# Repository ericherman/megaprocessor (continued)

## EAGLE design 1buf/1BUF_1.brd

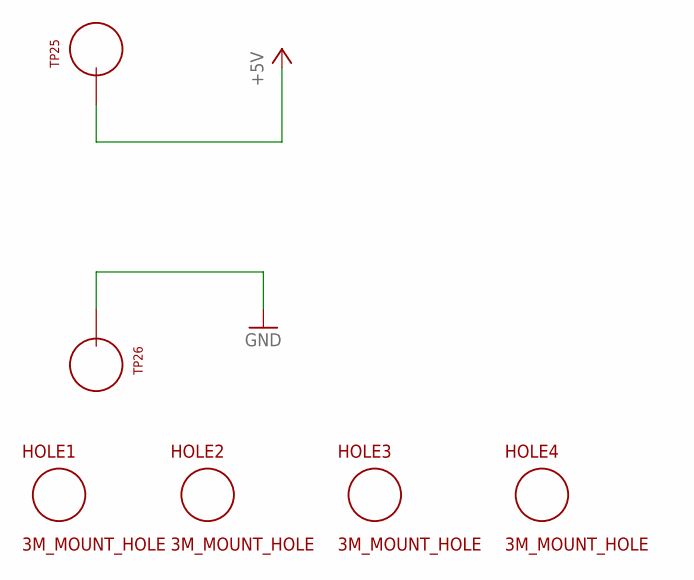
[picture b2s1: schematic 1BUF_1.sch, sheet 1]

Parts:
HOLE1, HOLE2, HOLE3, HOLE4: 3M_MOUNT_HOLE; 3M_HOLE
TP25, TP26: TEST_LOOP

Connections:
+5V: TP25.P$1; also elsewhere on the board
GND: TP26.P$1; also elsewhere on the board

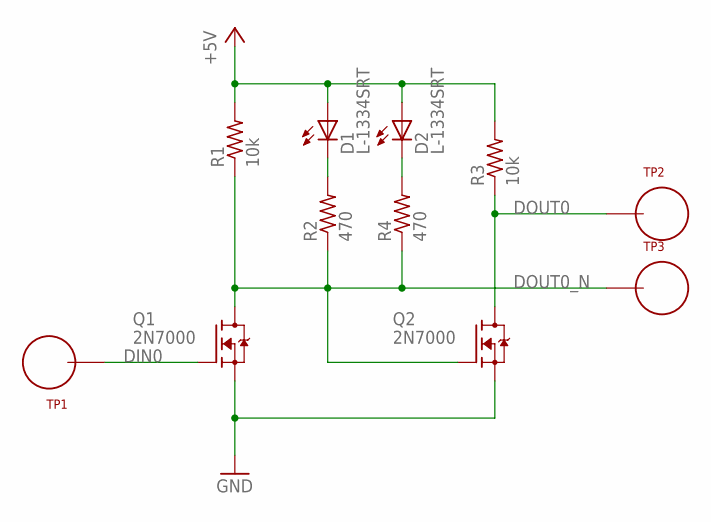
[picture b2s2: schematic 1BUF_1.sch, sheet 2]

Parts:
D1, D2: L-1334SRT; LED3MM
Q1, Q2: 2N7000; TO92-DGS
R1, R3: 10k; R_P2INCH
R2, R4: 470; R_P2INCH
TP1, TP2, TP3: TEST_LOOP

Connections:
+5V: D1.A, D2.A, R1.2, R3.2; also elsewhere on the board
DIN0: Q1.G, TP1.P$1
DOUT0: Q2.D, R3.1, TP2.P$1
DOUT0_N: Q1.D, Q2.G, R1.1, R2.1, R4.1, TP3.P$1
GND: Q1.S, Q2.S; also elsewhere on the board
unnamed: D2.K (C), R4.2
unnamed: D1.K (C), R2.2

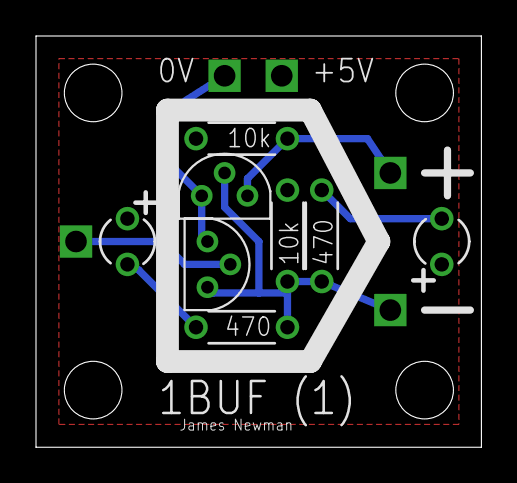
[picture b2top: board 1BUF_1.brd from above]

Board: 2 copper layers, 24.7 x 22.8 mm, 17 parts (0 on the bottom side), 7 nets.

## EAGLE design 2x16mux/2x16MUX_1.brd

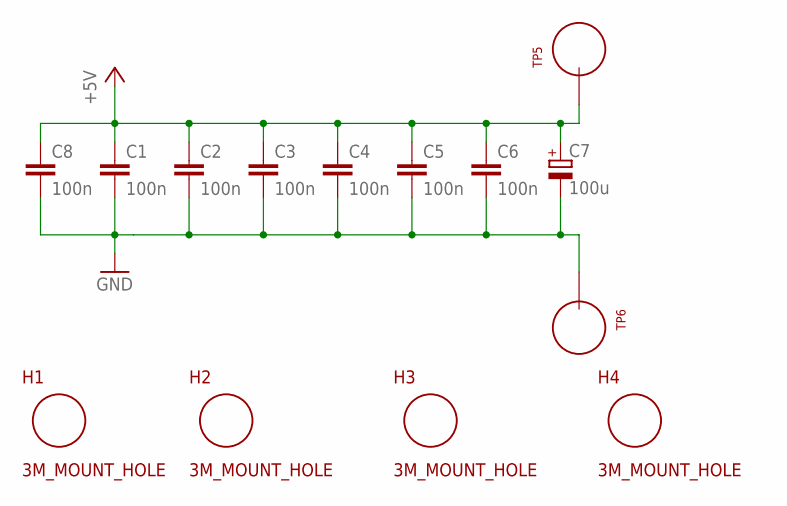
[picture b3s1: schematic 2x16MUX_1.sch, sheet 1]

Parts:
C1, C2, C3, C4, C5, C6, C8: 100n; CAP_P2INCH
C7: 100u; POLARISED_CAP_2P5_6P3MM
H1, H2, H3, H4: 3M_MOUNT_HOLE; 3M_HOLE
TP5, TP6: TEST_LOOP

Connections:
+5V: C1.1, C2.1, C3.1, C4.1, C5.1, C6.1, C7.A, C8.1, TP5.P$1; also elsewhere on the board
GND: C1.2, C2.2, C3.2, C4.2, C5.2, C6.2, C7.K, C8.2, TP6.P$1; also elsewhere on the board

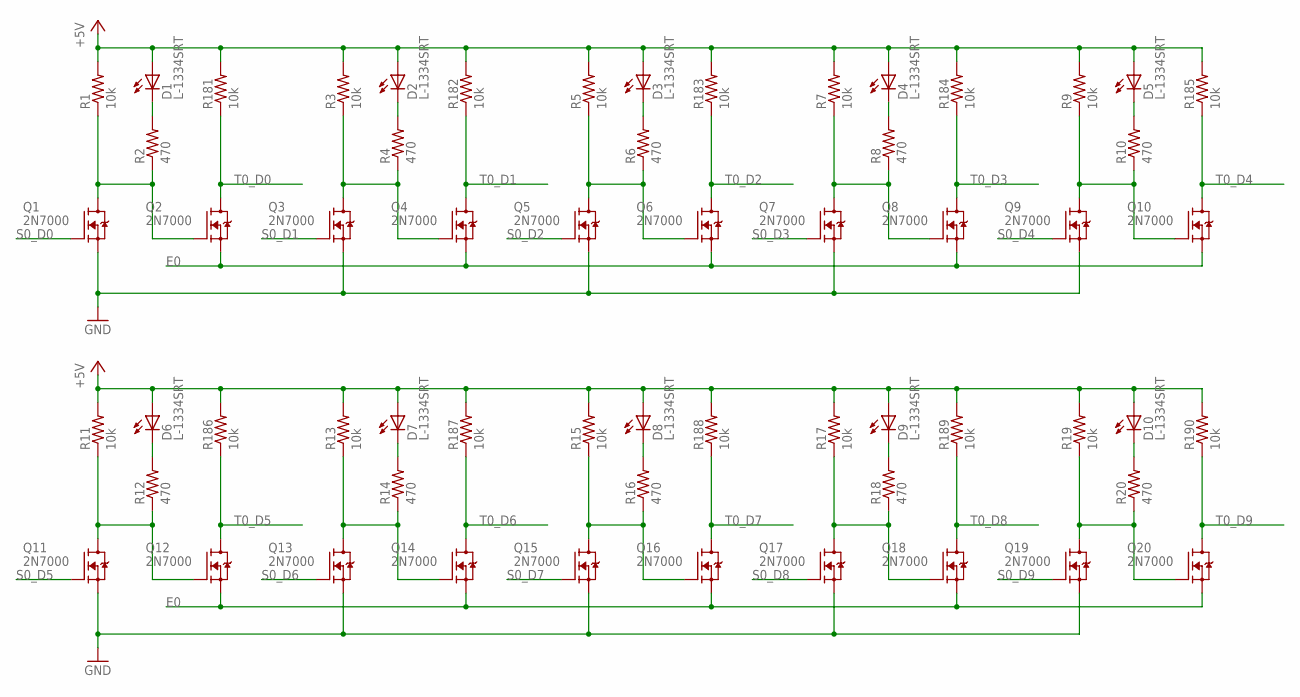
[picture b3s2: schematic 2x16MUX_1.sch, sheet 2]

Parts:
D1, D2, D3, D4, D5, D6, D7, D8, D9, D10: L-1334SRT; LED3MM
Q1, Q2, Q3, Q4, Q5, Q6, Q7, Q8, Q9, Q10, Q11, Q12, Q13, Q14, Q15, Q16, Q17, Q18, Q19, Q20: 2N7000; TO92-DGS
R1, R3, R5, R7, R9, R11, R13, R15, R17, R19, R181, R182, R183, R184, R185, R186, R187, R188, R189, R190: 10k; R_P2INCH
R2, R4, R6, R8, R10, R12, R14, R16, R18, R20: 470; R_P2INCH

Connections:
+5V: D1.A, D2.A, D3.A, D4.A, D5.A, D6.A, D7.A, D8.A, D9.A, D10.A, R1.2, R3.2, R5.2, R7.2, R9.2, R11.2, R13.2, R15.2, R17.2, R19.2, R181.2, R182.2, R183.2, R184.2, R185.2, R186.2, R187.2, R188.2, R189.2, R190.2; also elsewhere on the board
E0: Q2.S, Q4.S, Q6.S, Q8.S, Q10.S, Q12.S, Q14.S, Q16.S, Q18.S, Q20.S; also elsewhere on the board
GND: Q1.S, Q3.S, Q5.S, Q7.S, Q9.S, Q11.S, Q13.S, Q15.S, Q17.S, Q19.S; also elsewhere on the board
unnamed: Q3.D, Q4.G, R3.1, R4.1
unnamed: Q1.D, Q2.G, R1.1, R2.1
unnamed: D1.K (C), R2.2
unnamed: D2.K (C), R4.2
unnamed: Q5.D, Q6.G, R5.1, R6.1
unnamed: D3.K (C), R6.2
unnamed: Q7.D, Q8.G, R7.1, R8.1
unnamed: D4.K (C), R8.2
unnamed: Q9.D, Q10.G, R9.1, R10.1
unnamed: D5.K (C), R10.2
unnamed: Q11.D, Q12.G, R11.1, R12.1
unnamed: D6.K (C), R12.2
unnamed: Q13.D, Q14.G, R13.1, R14.1
unnamed: D7.K (C), R14.2
unnamed: Q15.D, Q16.G, R15.1, R16.1
unnamed: D8.K (C), R16.2
unnamed: Q17.D, Q18.G, R17.1, R18.1
unnamed: D9.K (C), R18.2
unnamed: Q19.D, Q20.G, R19.1, R20.1
unnamed: D10.K (C), R20.2
S0_D0: Q1.G; also elsewhere on the board
S0_D1: Q3.G; also elsewhere on the board
S0_D2: Q5.G; also elsewhere on the board
S0_D3: Q7.G; also elsewhere on the board
S0_D4: Q9.G; also elsewhere on the board
S0_D5: Q11.G; also elsewhere on the board
S0_D6: Q13.G; also elsewhere on the board
S0_D7: Q15.G; also elsewhere on the board
S0_D8: Q17.G; also elsewhere on the board
S0_D9: Q19.G; also elsewhere on the board
T0_D0: Q2.D, R181.1; also elsewhere on the board
T0_D1: Q4.D, R182.1; also elsewhere on the board
T0_D2: Q6.D, R183.1; also elsewhere on the board
T0_D3: Q8.D, R184.1; also elsewhere on the board
T0_D4: Q10.D, R185.1; also elsewhere on the board
T0_D5: Q12.D, R186.1; also elsewhere on the board
T0_D6: Q14.D, R187.1; also elsewhere on the board
T0_D7: Q16.D, R188.1; also elsewhere on the board
T0_D8: Q18.D, R189.1; also elsewhere on the board
T0_D9: Q20.D, R190.1; also elsewhere on the board

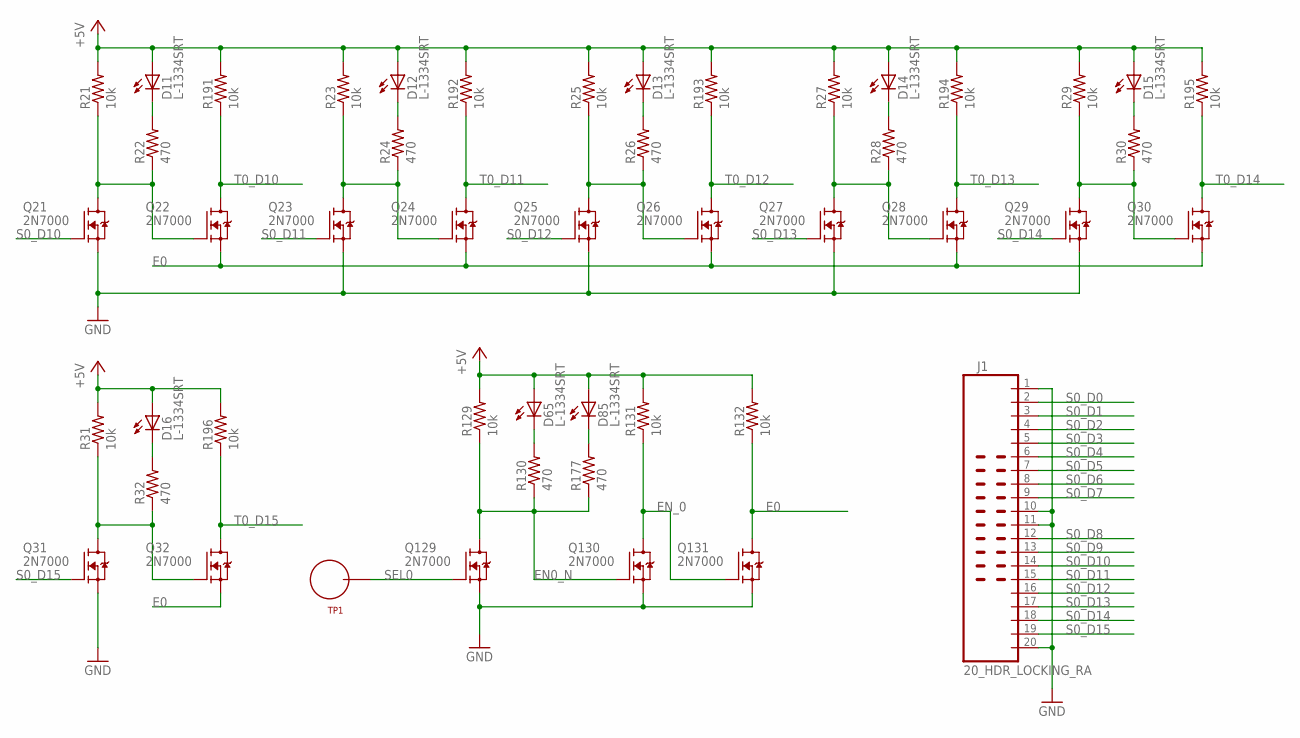
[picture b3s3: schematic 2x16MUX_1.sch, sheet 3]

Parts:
D11, D12, D13, D14, D15, D16, D65, D85: L-1334SRT; LED3MM
J1: 20_HDR_LOCKING_RA
Q21, Q22, Q23, Q24, Q25, Q26, Q27, Q28, Q29, Q30, Q31, Q32, Q129, Q130, Q131: 2N7000; TO92-DGS
R21, R23, R25, R27, R29, R31, R129, R131, R132, R191, R192, R193, R194, R195, R196: 10k; R_P2INCH
R22, R24, R26, R28, R30, R32, R130, R177: 470; R_P2INCH
TP1: TEST_LOOP

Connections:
+5V: D11.A, D12.A, D13.A, D14.A, D15.A, D16.A, D65.A, D85.A, R21.2, R23.2, R25.2, R27.2, R29.2, R31.2, R129.2, R131.2, R132.2, R191.2, R192.2, R193.2, R194.2, R195.2, R196.2; also elsewhere on the board
E0: Q22.S, Q24.S, Q26.S, Q28.S, Q30.S, Q32.S, Q131.D, R132.1; also elsewhere on the board
EN0_N: Q129.D, Q130.G, R129.1, R130.1, R177.1
EN_0: Q130.D, Q131.G, R131.1
GND: J1.1, J1.10, J1.11, J1.20, Q21.S, Q23.S, Q25.S, Q27.S, Q29.S, Q31.S, Q129.S, Q130.S, Q131.S; also elsewhere on the board
unnamed: Q21.D, Q22.G, R21.1, R22.1
unnamed: D11.K (C), R22.2
unnamed: Q23.D, Q24.G, R23.1, R24.1
unnamed: D12.K (C), R24.2
unnamed: Q25.D, Q26.G, R25.1, R26.1
unnamed: D13.K (C), R26.2
unnamed: Q27.D, Q28.G, R27.1, R28.1
unnamed: D14.K (C), R28.2
unnamed: Q29.D, Q30.G, R29.1, R30.1
unnamed: D15.K (C), R30.2
unnamed: Q31.D, Q32.G, R31.1, R32.1
unnamed: D16.K (C), R32.2
unnamed: D65.K (C), R130.2
unnamed: D85.K (C), R177.2
S0_D0: J1.2; also elsewhere on the board
S0_D1: J1.3; also elsewhere on the board
S0_D2: J1.4; also elsewhere on the board
S0_D3: J1.5; also elsewhere on the board
S0_D4: J1.6; also elsewhere on the board
S0_D5: J1.7; also elsewhere on the board
S0_D6: J1.8; also elsewhere on the board
S0_D7: J1.9; also elsewhere on the board
S0_D8: J1.12; also elsewhere on the board
S0_D9: J1.13; also elsewhere on the board
S0_D10: J1.14, Q21.G
S0_D11: J1.15, Q23.G
S0_D12: J1.16, Q25.G
S0_D13: J1.17, Q27.G
S0_D14: J1.18, Q29.G
S0_D15: J1.19, Q31.G
SEL0: Q129.G, TP1.P$1
T0_D10: Q22.D, R191.1; also elsewhere on the board
T0_D11: Q24.D, R192.1; also elsewhere on the board
T0_D12: Q26.D, R193.1; also elsewhere on the board
T0_D13: Q28.D, R194.1; also elsewhere on the board
T0_D14: Q30.D, R195.1; also elsewhere on the board
T0_D15: Q32.D, R196.1; also elsewhere on the board

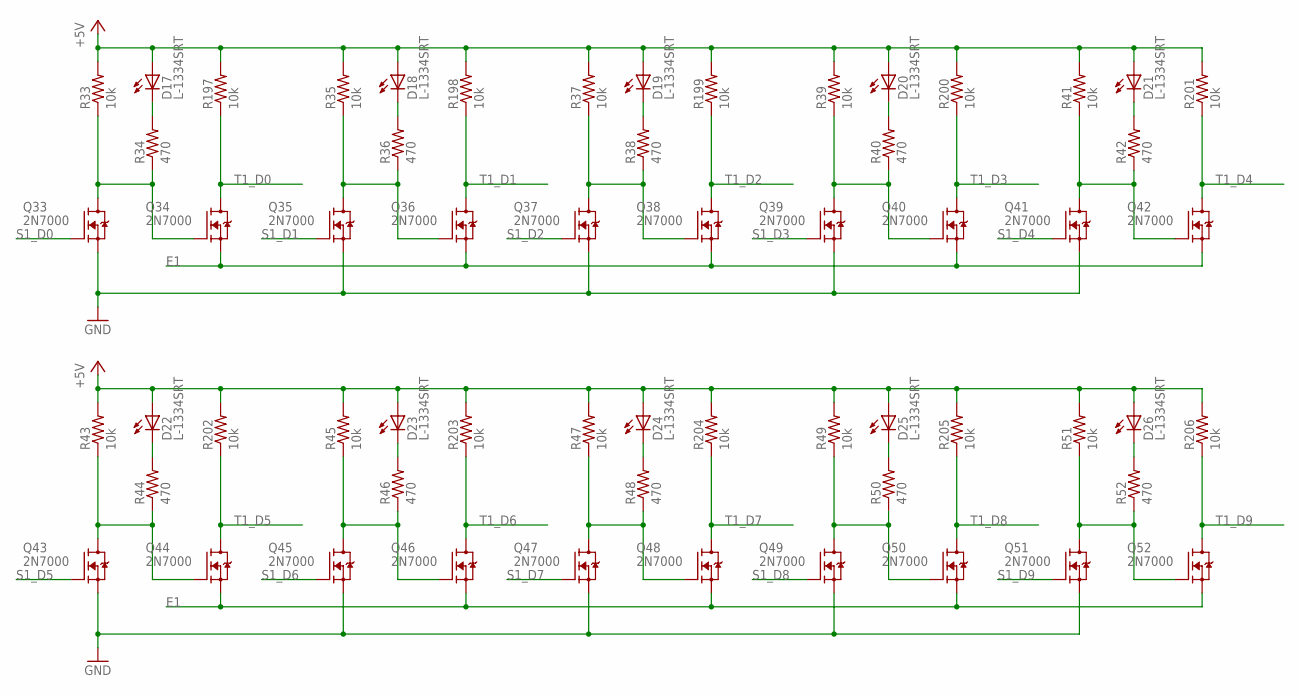
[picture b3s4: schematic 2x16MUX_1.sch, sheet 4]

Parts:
D17, D18, D19, D20, D21, D22, D23, D24, D25, D26: L-1334SRT; LED3MM
Q33, Q34, Q35, Q36, Q37, Q38, Q39, Q40, Q41, Q42, Q43, Q44, Q45, Q46, Q47, Q48, Q49, Q50, Q51, Q52: 2N7000; TO92-DGS
R33, R35, R37, R39, R41, R43, R45, R47, R49, R51, R197, R198, R199, R200, R201, R202, R203, R204, R205, R206: 10k; R_P2INCH
R34, R36, R38, R40, R42, R44, R46, R48, R50, R52: 470; R_P2INCH

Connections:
+5V: D17.A, D18.A, D19.A, D20.A, D21.A, D22.A, D23.A, D24.A, D25.A, D26.A, R33.2, R35.2, R37.2, R39.2, R41.2, R43.2, R45.2, R47.2, R49.2, R51.2, R197.2, R198.2, R199.2, R200.2, R201.2, R202.2, R203.2, R204.2, R205.2, R206.2; also elsewhere on the board
E1: Q34.S, Q36.S, Q38.S, Q40.S, Q42.S, Q44.S, Q46.S, Q48.S, Q50.S, Q52.S; also elsewhere on the board
GND: Q33.S, Q35.S, Q37.S, Q39.S, Q41.S, Q43.S, Q45.S, Q47.S, Q49.S, Q51.S; also elsewhere on the board
unnamed: Q33.D, Q34.G, R33.1, R34.1
unnamed: D17.K (C), R34.2
unnamed: Q35.D, Q36.G, R35.1, R36.1
unnamed: D18.K (C), R36.2
unnamed: Q37.D, Q38.G, R37.1, R38.1
unnamed: D19.K (C), R38.2
unnamed: Q39.D, Q40.G, R39.1, R40.1
unnamed: D20.K (C), R40.2
unnamed: Q41.D, Q42.G, R41.1, R42.1
unnamed: D21.K (C), R42.2
unnamed: Q43.D, Q44.G, R43.1, R44.1
unnamed: D22.K (C), R44.2
unnamed: Q45.D, Q46.G, R45.1, R46.1
unnamed: D23.K (C), R46.2
unnamed: Q47.D, Q48.G, R47.1, R48.1
unnamed: D24.K (C), R48.2
unnamed: Q49.D, Q50.G, R49.1, R50.1
unnamed: D25.K (C), R50.2
unnamed: Q51.D, Q52.G, R51.1, R52.1
unnamed: D26.K (C), R52.2
S1_D0: Q33.G; also elsewhere on the board
S1_D1: Q35.G; also elsewhere on the board
S1_D2: Q37.G; also elsewhere on the board
S1_D3: Q39.G; also elsewhere on the board
S1_D4: Q41.G; also elsewhere on the board
S1_D5: Q43.G; also elsewhere on the board
S1_D6: Q45.G; also elsewhere on the board
S1_D7: Q47.G; also elsewhere on the board
S1_D8: Q49.G; also elsewhere on the board
S1_D9: Q51.G; also elsewhere on the board
T1_D0: Q34.D, R197.1; also elsewhere on the board
T1_D1: Q36.D, R198.1; also elsewhere on the board
T1_D2: Q38.D, R199.1; also elsewhere on the board
T1_D3: Q40.D, R200.1; also elsewhere on the board
T1_D4: Q42.D, R201.1; also elsewhere on the board
T1_D5: Q44.D, R202.1; also elsewhere on the board
T1_D6: Q46.D, R203.1; also elsewhere on the board
T1_D7: Q48.D, R204.1; also elsewhere on the board
T1_D8: Q50.D, R205.1; also elsewhere on the board
T1_D9: Q52.D, R206.1; also elsewhere on the board

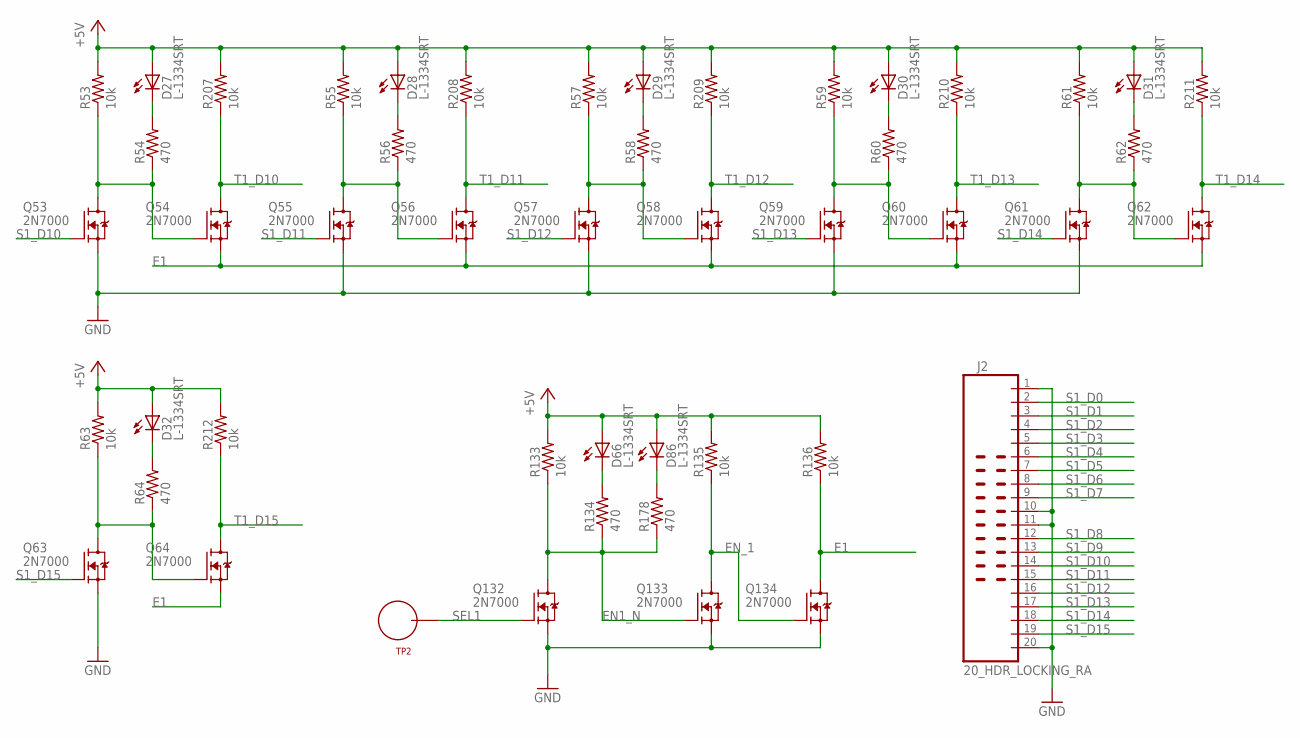
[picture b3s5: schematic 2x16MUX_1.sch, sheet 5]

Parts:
D27, D28, D29, D30, D31, D32, D66, D86: L-1334SRT; LED3MM
J2: 20_HDR_LOCKING_RA
Q53, Q54, Q55, Q56, Q57, Q58, Q59, Q60, Q61, Q62, Q63, Q64, Q132, Q133, Q134: 2N7000; TO92-DGS
R53, R55, R57, R59, R61, R63, R133, R135, R136, R207, R208, R209, R210, R211, R212: 10k; R_P2INCH
R54, R56, R58, R60, R62, R64, R134, R178: 470; R_P2INCH
TP2: TEST_LOOP

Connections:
+5V: D27.A, D28.A, D29.A, D30.A, D31.A, D32.A, D66.A, D86.A, R53.2, R55.2, R57.2, R59.2, R61.2, R63.2, R133.2, R135.2, R136.2, R207.2, R208.2, R209.2, R210.2, R211.2, R212.2; also elsewhere on the board
E1: Q54.S, Q56.S, Q58.S, Q60.S, Q62.S, Q64.S, Q134.D, R136.1; also elsewhere on the board
EN1_N: Q132.D, Q133.G, R133.1, R134.1, R178.1
EN_1: Q133.D, Q134.G, R135.1
GND: J2.1, J2.10, J2.11, J2.20, Q53.S, Q55.S, Q57.S, Q59.S, Q61.S, Q63.S, Q132.S, Q133.S, Q134.S; also elsewhere on the board
unnamed: Q53.D, Q54.G, R53.1, R54.1
unnamed: D27.K (C), R54.2
unnamed: Q55.D, Q56.G, R55.1, R56.1
unnamed: D28.K (C), R56.2
unnamed: Q57.D, Q58.G, R57.1, R58.1
unnamed: D29.K (C), R58.2
unnamed: Q59.D, Q60.G, R59.1, R60.1
unnamed: D30.K (C), R60.2
unnamed: Q61.D, Q62.G, R61.1, R62.1
unnamed: D31.K (C), R62.2
unnamed: Q63.D, Q64.G, R63.1, R64.1
unnamed: D32.K (C), R64.2
unnamed: D66.K (C), R134.2
unnamed: D86.K (C), R178.2
S1_D0: J2.2; also elsewhere on the board
S1_D1: J2.3; also elsewhere on the board
S1_D2: J2.4; also elsewhere on the board
S1_D3: J2.5; also elsewhere on the board
S1_D4: J2.6; also elsewhere on the board
S1_D5: J2.7; also elsewhere on the board
S1_D6: J2.8; also elsewhere on the board
S1_D7: J2.9; also elsewhere on the board
S1_D8: J2.12; also elsewhere on the board
S1_D9: J2.13; also elsewhere on the board
S1_D10: J2.14, Q53.G
S1_D11: J2.15, Q55.G
S1_D12: J2.16, Q57.G
S1_D13: J2.17, Q59.G
S1_D14: J2.18, Q61.G
S1_D15: J2.19, Q63.G
SEL1: Q132.G, TP2.P$1
T1_D10: Q54.D, R207.1; also elsewhere on the board
T1_D11: Q56.D, R208.1; also elsewhere on the board
T1_D12: Q58.D, R209.1; also elsewhere on the board
T1_D13: Q60.D, R210.1; also elsewhere on the board
T1_D14: Q62.D, R211.1; also elsewhere on the board
T1_D15: Q64.D, R212.1; also elsewhere on the board

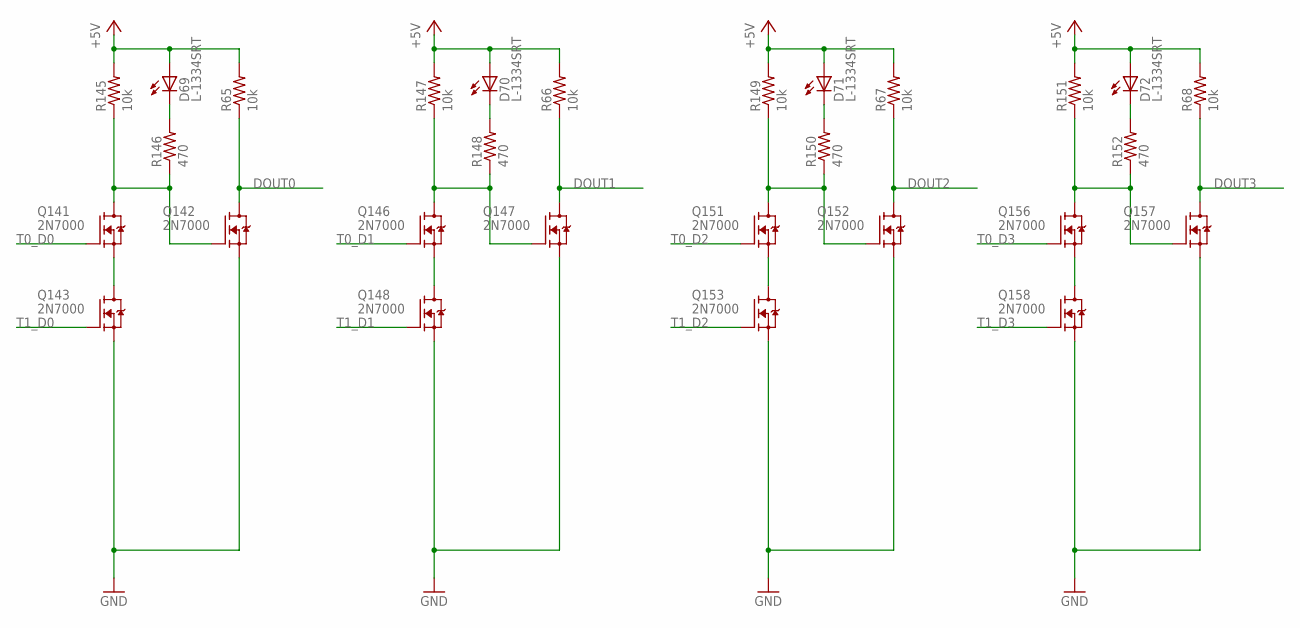
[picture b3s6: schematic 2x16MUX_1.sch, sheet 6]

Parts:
D69, D70, D71, D72: L-1334SRT; LED3MM
Q141, Q142, Q143, Q146, Q147, Q148, Q151, Q152, Q153, Q156, Q157, Q158: 2N7000; TO92-DGS
R65, R66, R67, R68, R145, R147, R149, R151: 10k; R_P2INCH
R146, R148, R150, R152: 470; R_P2INCH

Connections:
+5V: D69.A, D70.A, D71.A, D72.A, R65.2, R66.2, R67.2, R68.2, R145.2, R147.2, R149.2, R151.2; also elsewhere on the board
DOUT0: Q142.D, R65.1; also elsewhere on the board
DOUT1: Q147.D, R66.1; also elsewhere on the board
DOUT2: Q152.D, R67.1; also elsewhere on the board
DOUT3: Q157.D, R68.1; also elsewhere on the board
GND: Q142.S, Q143.S, Q147.S, Q148.S, Q152.S, Q153.S, Q157.S, Q158.S; also elsewhere on the board
unnamed: Q141.D, Q142.G, R145.1, R146.1
unnamed: D69.K (C), R146.2
unnamed: Q141.S, Q143.D
unnamed: Q146.D, Q147.G, R147.1, R148.1
unnamed: D70.K (C), R148.2
unnamed: Q146.S, Q148.D
unnamed: Q151.D, Q152.G, R149.1, R150.1
unnamed: D71.K (C), R150.2
unnamed: Q151.S, Q153.D
unnamed: Q156.D, Q157.G, R151.1, R152.1
unnamed: D72.K (C), R152.2
unnamed: Q156.S, Q158.D
T0_D0: Q141.G; also elsewhere on the board
T0_D1: Q146.G; also elsewhere on the board
T0_D2: Q151.G; also elsewhere on the board
T0_D3: Q156.G; also elsewhere on the board
T1_D0: Q143.G; also elsewhere on the board
T1_D1: Q148.G; also elsewhere on the board
T1_D2: Q153.G; also elsewhere on the board
T1_D3: Q158.G; also elsewhere on the board

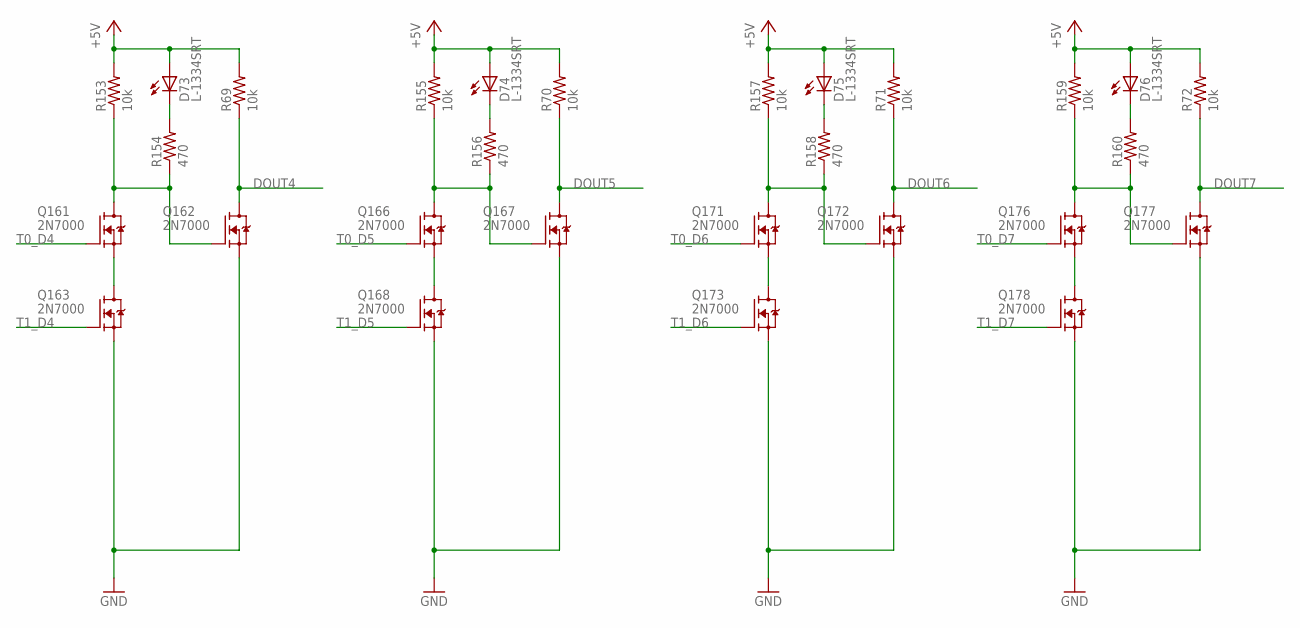
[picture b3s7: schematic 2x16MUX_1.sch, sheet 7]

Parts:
D73, D74, D75, D76: L-1334SRT; LED3MM
Q161, Q162, Q163, Q166, Q167, Q168, Q171, Q172, Q173, Q176, Q177, Q178: 2N7000; TO92-DGS
R69, R70, R71, R72, R153, R155, R157, R159: 10k; R_P2INCH
R154, R156, R158, R160: 470; R_P2INCH

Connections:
+5V: D73.A, D74.A, D75.A, D76.A, R69.2, R70.2, R71.2, R72.2, R153.2, R155.2, R157.2, R159.2; also elsewhere on the board
DOUT4: Q162.D, R69.1; also elsewhere on the board
DOUT5: Q167.D, R70.1; also elsewhere on the board
DOUT6: Q172.D, R71.1; also elsewhere on the board
DOUT7: Q177.D, R72.1; also elsewhere on the board
GND: Q162.S, Q163.S, Q167.S, Q168.S, Q172.S, Q173.S, Q177.S, Q178.S; also elsewhere on the board
unnamed: Q161.D, Q162.G, R153.1, R154.1
unnamed: D73.K (C), R154.2
unnamed: Q161.S, Q163.D
unnamed: Q166.D, Q167.G, R155.1, R156.1
unnamed: D74.K (C), R156.2
unnamed: Q166.S, Q168.D
unnamed: Q171.D, Q172.G, R157.1, R158.1
unnamed: D75.K (C), R158.2
unnamed: Q171.S, Q173.D
unnamed: Q176.D, Q177.G, R159.1, R160.1
unnamed: D76.K (C), R160.2
unnamed: Q176.S, Q178.D
T0_D4: Q161.G; also elsewhere on the board
T0_D5: Q166.G; also elsewhere on the board
T0_D6: Q171.G; also elsewhere on the board
T0_D7: Q176.G; also elsewhere on the board
T1_D4: Q163.G; also elsewhere on the board
T1_D5: Q168.G; also elsewhere on the board
T1_D6: Q173.G; also elsewhere on the board
T1_D7: Q178.G; also elsewhere on the board

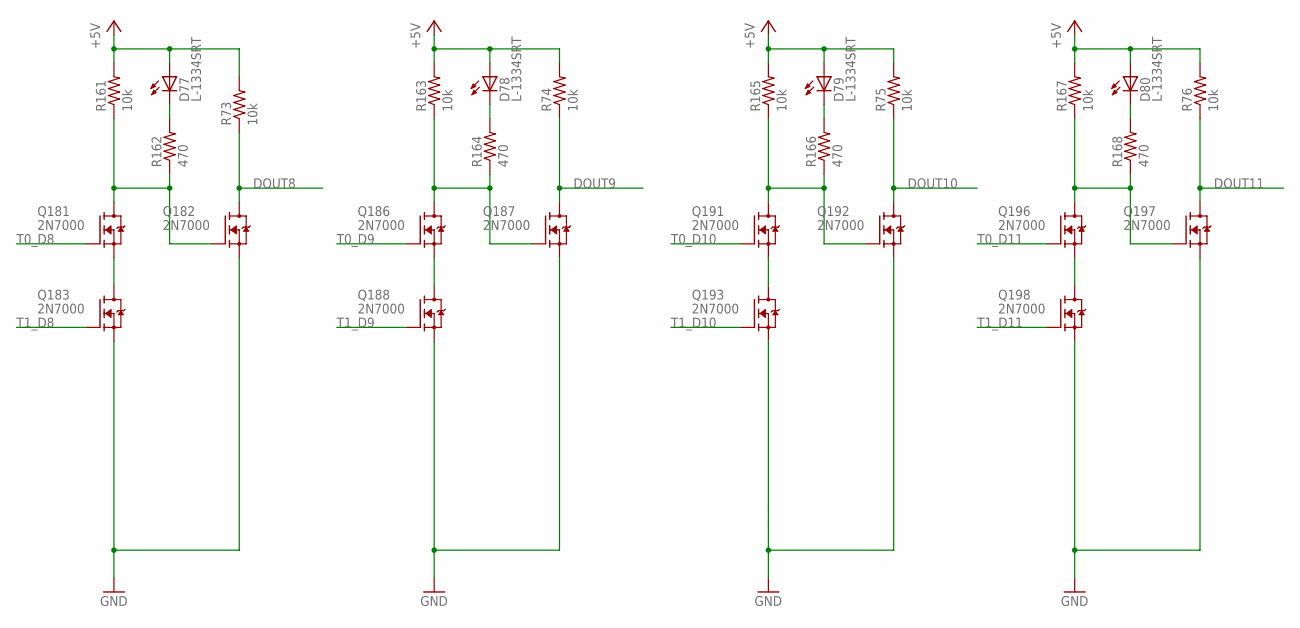
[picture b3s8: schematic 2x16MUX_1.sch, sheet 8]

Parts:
D77, D78, D79, D80: L-1334SRT; LED3MM
Q181, Q182, Q183, Q186, Q187, Q188, Q191, Q192, Q193, Q196, Q197, Q198: 2N7000; TO92-DGS
R73, R74, R75, R76, R161, R163, R165, R167: 10k; R_P2INCH
R162, R164, R166, R168: 470; R_P2INCH

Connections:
+5V: D77.A, D78.A, D79.A, D80.A, R73.2, R74.2, R75.2, R76.2, R161.2, R163.2, R165.2, R167.2; also elsewhere on the board
DOUT8: Q182.D, R73.1; also elsewhere on the board
DOUT9: Q187.D, R74.1; also elsewhere on the board
DOUT10: Q192.D, R75.1; also elsewhere on the board
DOUT11: Q197.D, R76.1; also elsewhere on the board
GND: Q182.S, Q183.S, Q187.S, Q188.S, Q192.S, Q193.S, Q197.S, Q198.S; also elsewhere on the board
unnamed: Q181.D, Q182.G, R161.1, R162.1
unnamed: D77.K (C), R162.2
unnamed: Q181.S, Q183.D
unnamed: Q186.D, Q187.G, R163.1, R164.1
unnamed: D78.K (C), R164.2
unnamed: Q186.S, Q188.D
unnamed: Q191.D, Q192.G, R165.1, R166.1
unnamed: D79.K (C), R166.2
unnamed: Q191.S, Q193.D
unnamed: Q196.D, Q197.G, R167.1, R168.1
unnamed: D80.K (C), R168.2
unnamed: Q196.S, Q198.D
T0_D8: Q181.G; also elsewhere on the board
T0_D9: Q186.G; also elsewhere on the board
T0_D10: Q191.G; also elsewhere on the board
T0_D11: Q196.G; also elsewhere on the board
T1_D8: Q183.G; also elsewhere on the board
T1_D9: Q188.G; also elsewhere on the board
T1_D10: Q193.G; also elsewhere on the board
T1_D11: Q198.G; also elsewhere on the board

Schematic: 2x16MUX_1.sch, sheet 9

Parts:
D81, D82, D83, D84: L-1334SRT; LED3MM
Q201, Q202, Q203, Q206, Q207, Q208, Q211, Q212, Q213, Q216, Q217, Q218: 2N7000; TO92-DGS
R77, R78, R79, R80, R169, R171, R173, R175: 10k; R_P2INCH
R170, R172, R174, R176: 470; R_P2INCH

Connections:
+5V: D81.A, D82.A, D83.A, D84.A, R77.2, R78.2, R79.2, R80.2, R169.2, R171.2, R173.2, R175.2; also elsewhere on the board
DOUT12: Q202.D, R77.1; also elsewhere on the board
DOUT13: Q207.D, R78.1; also elsewhere on the board
DOUT14: Q212.D, R79.1; also elsewhere on the board
DOUT15: Q217.D, R80.1; also elsewhere on the board
GND: Q202.S, Q203.S, Q207.S, Q208.S, Q212.S, Q213.S, Q217.S, Q218.S; also elsewhere on the board
unnamed: Q201.D, Q202.G, R169.1, R170.1
unnamed: D81.K (C), R170.2
unnamed: Q201.S, Q203.D
unnamed: Q206.D, Q207.G, R171.1, R172.1
unnamed: D82.K (C), R172.2
unnamed: Q206.S, Q208.D
unnamed: Q211.D, Q212.G, R173.1, R174.1
unnamed: D83.K (C), R174.2
unnamed: Q211.S, Q213.D
unnamed: Q216.D, Q217.G, R175.1, R176.1
unnamed: D84.K (C), R176.2
unnamed: Q216.S, Q218.D
T0_D12: Q201.G; also elsewhere on the board
T0_D13: Q206.G; also elsewhere on the board
T0_D14: Q211.G; also elsewhere on the board
T0_D15: Q216.G; also elsewhere on the board
T1_D12: Q203.G; also elsewhere on the board
T1_D13: Q208.G; also elsewhere on the board
T1_D14: Q213.G; also elsewhere on the board
T1_D15: Q218.G; also elsewhere on the board

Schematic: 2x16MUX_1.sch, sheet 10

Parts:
J5: 20_HDR_LOCKING_RA

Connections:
DOUT0: J5.2; also elsewhere on the board
DOUT1: J5.3; also elsewhere on the board
DOUT2: J5.4; also elsewhere on the board
DOUT3: J5.5; also elsewhere on the board
DOUT4: J5.6; also elsewhere on the board
DOUT5: J5.7; also elsewhere on the board
DOUT6: J5.8; also elsewhere on the board
DOUT7: J5.9; also elsewhere on the board
DOUT8: J5.12; also elsewhere on the board
DOUT9: J5.13; also elsewhere on the board
DOUT10: J5.14; also elsewhere on the board
DOUT11: J5.15; also elsewhere on the board
DOUT12: J5.16; also elsewhere on the board
DOUT13: J5.17; also elsewhere on the board
DOUT14: J5.18; also elsewhere on the board
DOUT15: J5.19; also elsewhere on the board
GND: J5.1, J5.10, J5.11, J5.20; also elsewhere on the board

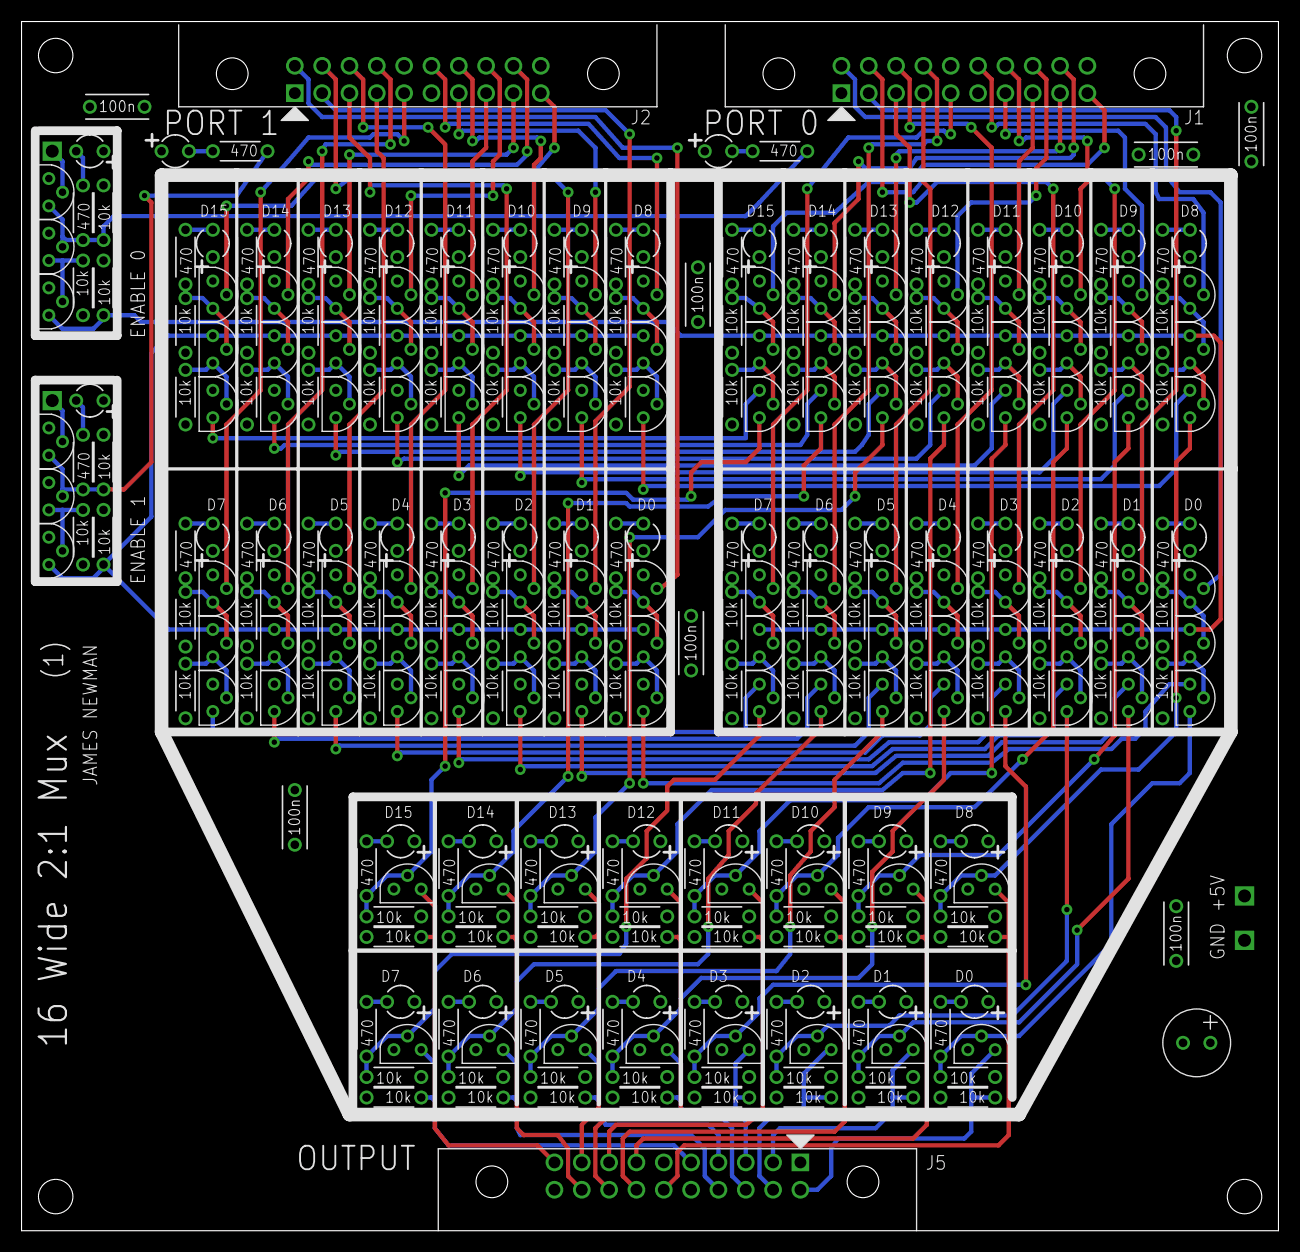
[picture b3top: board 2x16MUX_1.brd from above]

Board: 4 copper layers, 116.8 x 112.4 mm, 343 parts (0 on the bottom side), 206 nets.

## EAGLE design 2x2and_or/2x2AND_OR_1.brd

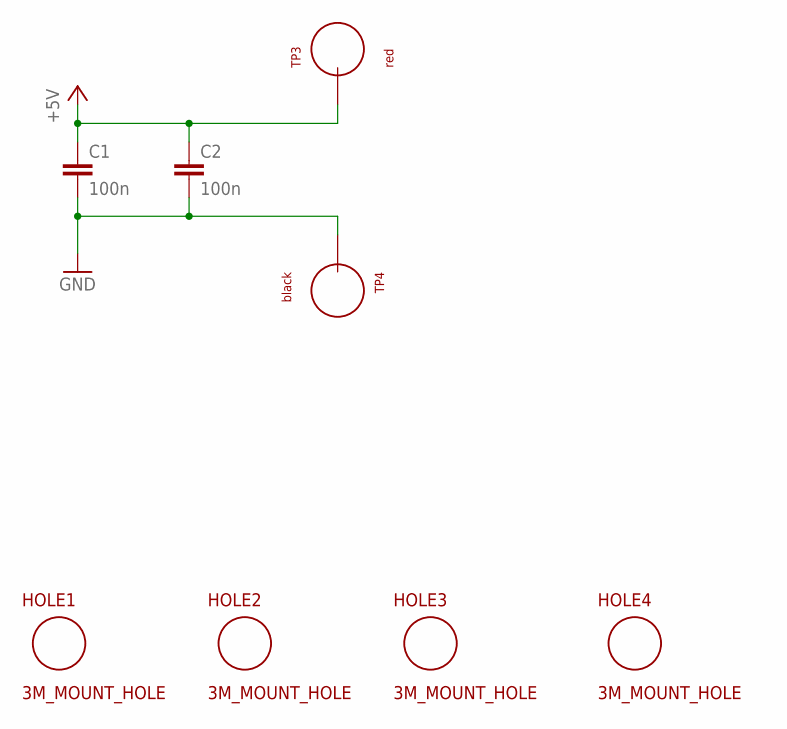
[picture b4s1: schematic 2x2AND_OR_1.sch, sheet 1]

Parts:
C1, C2: 100n; CAP_P2INCH
HOLE1, HOLE2, HOLE3, HOLE4: 3M_MOUNT_HOLE; 3M_HOLE
TP3: red; TEST_LOOP
TP4: black; TEST_LOOP

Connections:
+5V: C1.1, C2.1, TP3.P$1; also elsewhere on the board
GND: C1.2, C2.2, TP4.P$1; also elsewhere on the board

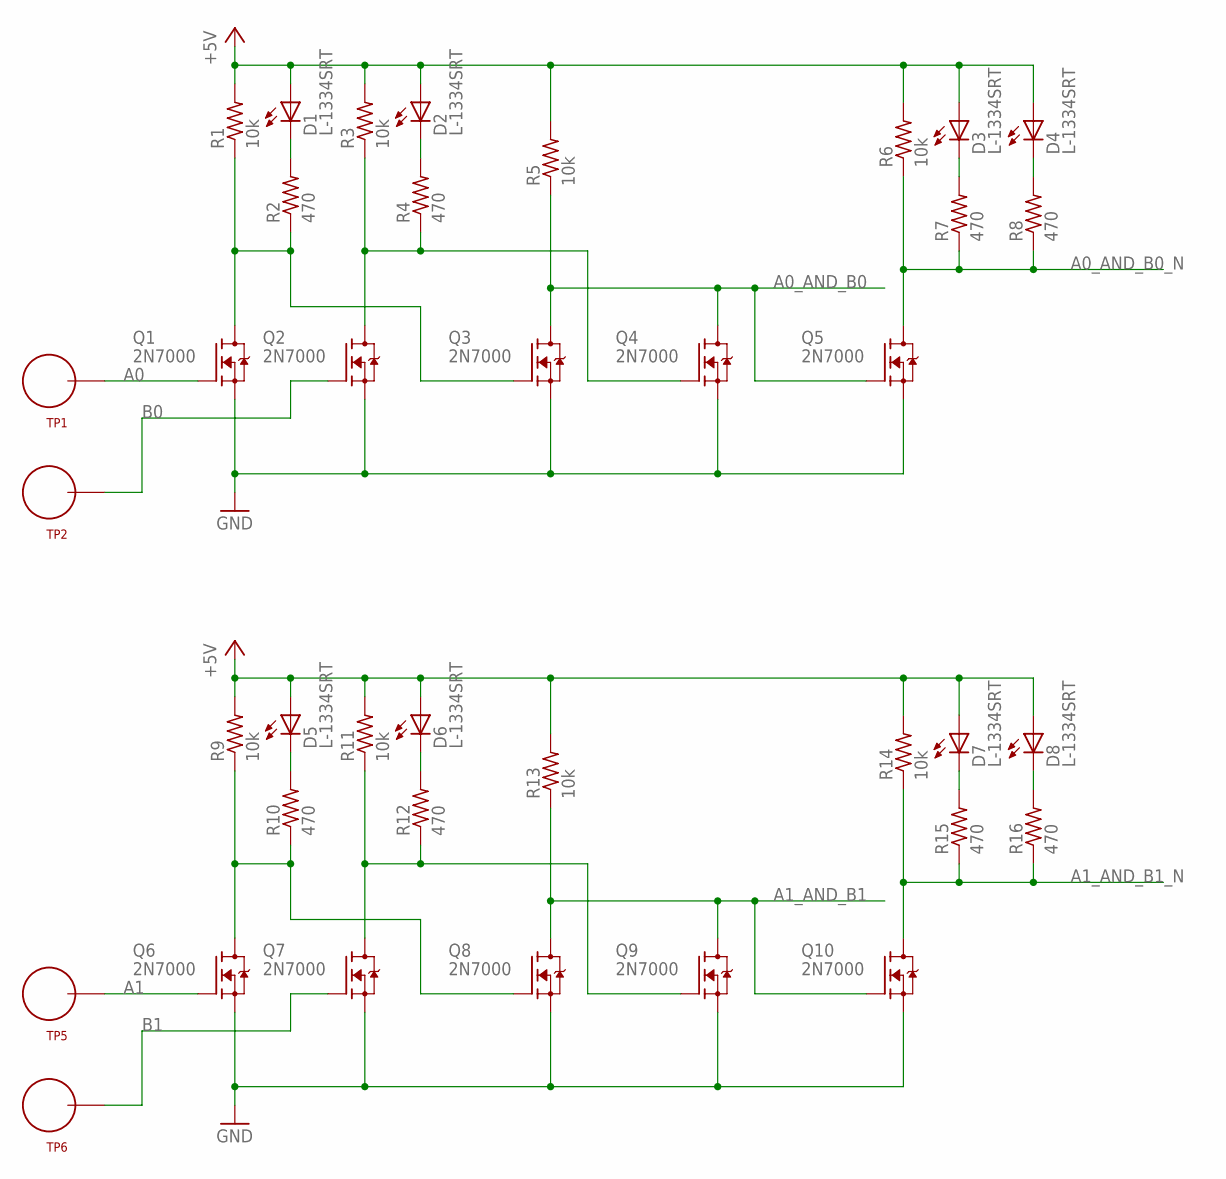
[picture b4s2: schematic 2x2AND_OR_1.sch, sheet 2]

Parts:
D1, D2, D3, D4, D5, D6, D7, D8: L-1334SRT; LED3MM
Q1, Q2, Q3, Q4, Q5, Q6, Q7, Q8, Q9, Q10: 2N7000; TO92-DGS
R1, R3, R5, R6, R9, R11, R13, R14: 10k; R_P2INCH
R2, R4, R7, R8, R10, R12, R15, R16: 470; R_P2INCH
TP1, TP2, TP5, TP6: TEST_LOOP

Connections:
+5V: D1.A, D2.A, D3.A, D4.A, D5.A, D6.A, D7.A, D8.A, R1.2, R3.2, R5.2, R6.2, R9.2, R11.2, R13.2, R14.2; also elsewhere on the board
A0: Q1.G, TP1.P$1
A0_AND_B0: Q3.D, Q4.D, Q5.G, R5.1; also elsewhere on the board
A0_AND_B0_N: Q5.D, R6.1, R7.1, R8.1
A1: Q6.G, TP5.P$1
A1_AND_B1: Q8.D, Q9.D, Q10.G, R13.1; also elsewhere on the board
A1_AND_B1_N: Q10.D, R14.1, R15.1, R16.1
B0: Q2.G, TP2.P$1
B1: Q7.G, TP6.P$1
GND: Q1.S, Q2.S, Q3.S, Q4.S, Q5.S, Q6.S, Q7.S, Q8.S, Q9.S, Q10.S; also elsewhere on the board
unnamed: D1.K (C), R2.2
unnamed: Q1.D, Q3.G, R1.1, R2.1
unnamed: D4.K (C), R8.2
unnamed: D2.K (C), R4.2
unnamed: Q2.D, Q4.G, R3.1, R4.1
unnamed: D5.K (C), R10.2
unnamed: Q6.D, Q8.G, R9.1, R10.1
unnamed: D6.K (C), R12.2
unnamed: D3.K (C), R7.2
unnamed: Q7.D, Q9.G, R11.1, R12.1
unnamed: D7.K (C), R15.2
unnamed: D8.K (C), R16.2
